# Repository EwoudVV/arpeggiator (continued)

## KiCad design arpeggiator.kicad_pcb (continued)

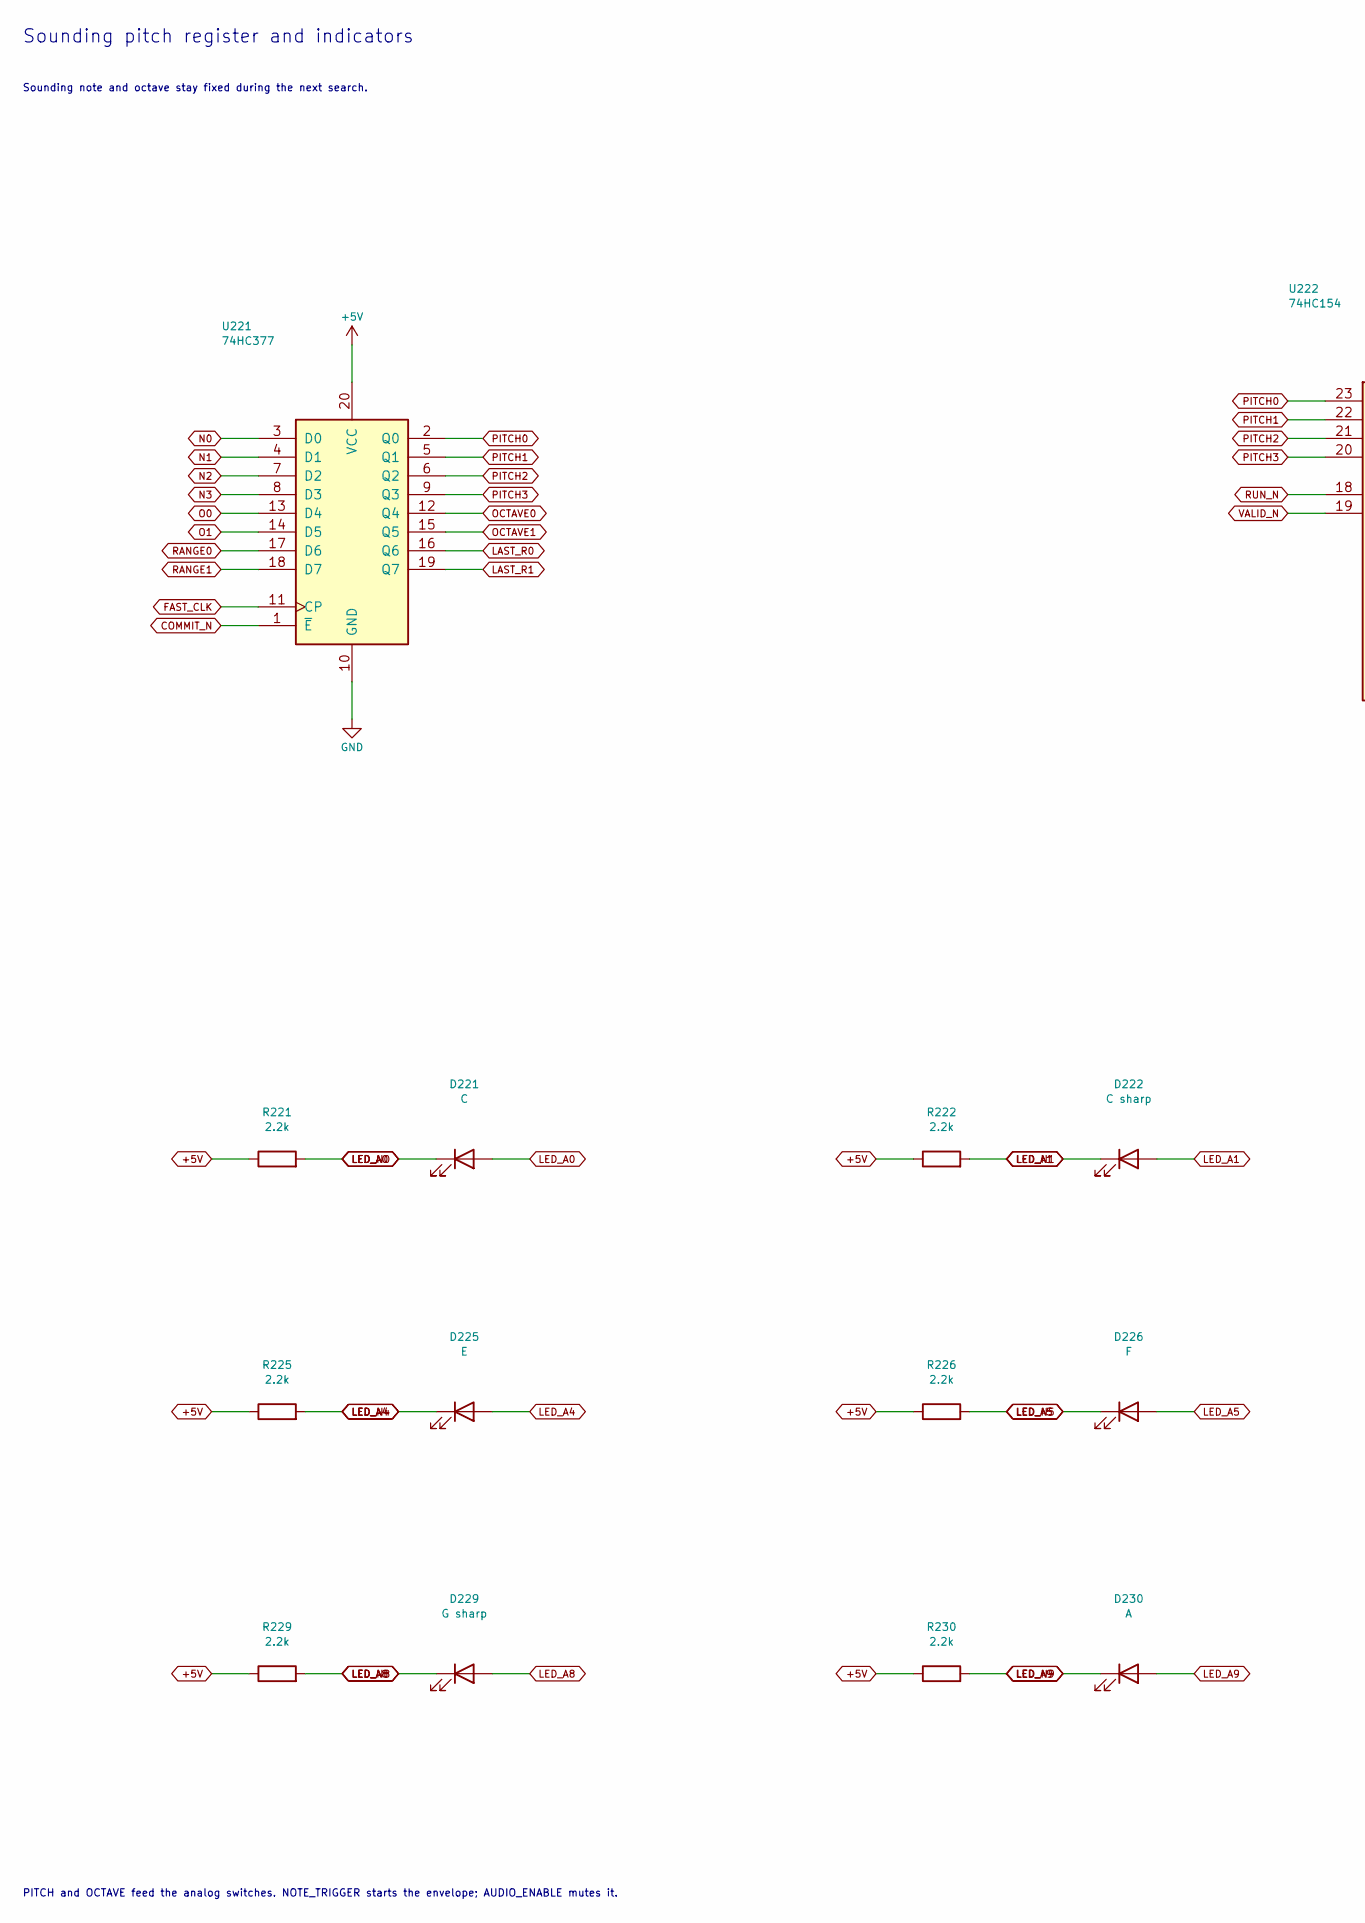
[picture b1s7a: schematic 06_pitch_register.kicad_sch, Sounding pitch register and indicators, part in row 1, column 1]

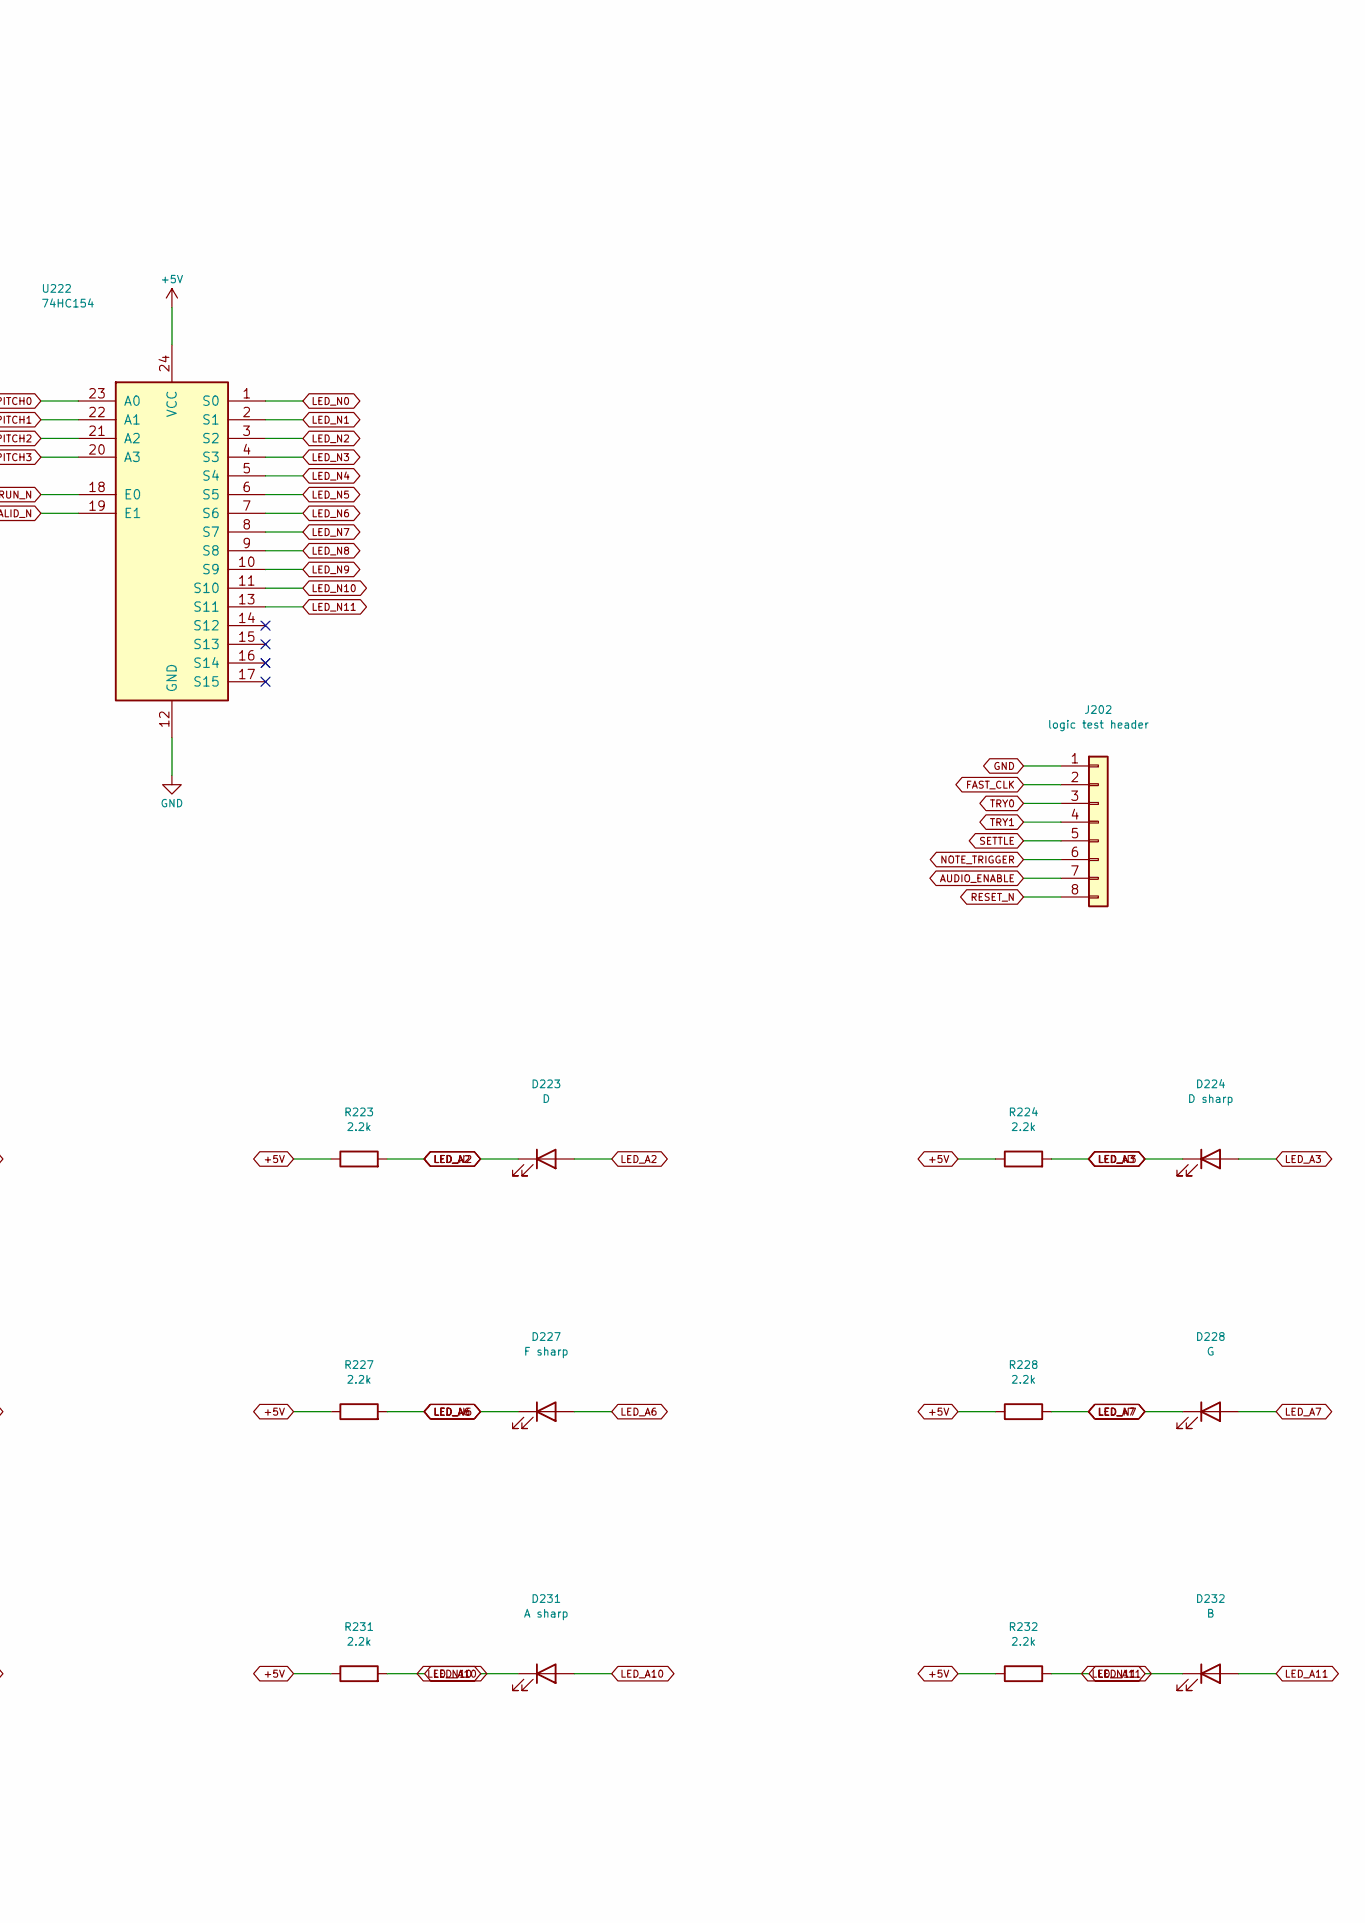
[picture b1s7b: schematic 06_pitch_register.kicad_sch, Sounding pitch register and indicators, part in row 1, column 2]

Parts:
D221: C; LED_0805_2012Metric
D222: C sharp; LED_0805_2012Metric
D223: D; LED_0805_2012Metric
D224: D sharp; LED_0805_2012Metric
D225: E; LED_0805_2012Metric
D226: F; LED_0805_2012Metric
D227: F sharp; LED_0805_2012Metric
D228: G; LED_0805_2012Metric
D229: G sharp; LED_0805_2012Metric
D230: A; LED_0805_2012Metric
D231: A sharp; LED_0805_2012Metric
D232: B; LED_0805_2012Metric
J202: logic test header; PinHeader_1x08_P2.54mm_Vertical
R221, R222, R223, R224, R225, R226, R227, R228, R229, R230, R231, R232: 2.2k; R_0805_2012Metric
U221: 74HC377; SOIC-20W_7.5x12.8mm_P1.27mm; MPN 74HC377D,653
U222: 74HC154; SOIC-24W_7.5x15.4mm_P1.27mm; MPN CD74HC154M96

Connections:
+5V: R221.1, R222.1, R223.1, R224.1, R225.1, R226.1, R227.1, R228.1, R229.1, R230.1, R231.1, R232.1, U221.20 (VCC), U222.24 (VCC); also elsewhere on the board
AUDIO_ENABLE: J202.7; also elsewhere on the board
COMMIT_N: U221.1 (~E); also elsewhere on the board
FAST_CLK: J202.2, U221.11 (CP); also elsewhere on the board
LAST_R0: U221.16 (Q6); also elsewhere on the board
LAST_R1: U221.19 (Q7); also elsewhere on the board
LED_A0: D221.2 (A), R221.2
LED_A1: D222.2 (A), R222.2
LED_A2: D223.2 (A), R223.2
LED_A3: D224.2 (A), R224.2
LED_A4: D225.2 (A), R225.2
LED_A5: D226.2 (A), R226.2
LED_A6: D227.2 (A), R227.2
LED_A7: D228.2 (A), R228.2
LED_A8: D229.2 (A), R229.2
LED_A9: D230.2 (A), R230.2
LED_A10: D231.2 (A), R231.2
LED_A11: D232.2 (A), R232.2
LED_N0: D221.1 (K), U222.1 (S0)
LED_N1: D222.1 (K), U222.2 (S1)
LED_N2: D223.1 (K), U222.3 (S2)
LED_N3: D224.1 (K), U222.4 (S3)
LED_N4: D225.1 (K), U222.5 (S4)
LED_N5: D226.1 (K), U222.6 (S5)
LED_N6: D227.1 (K), U222.7 (S6)
LED_N7: D228.1 (K), U222.8 (S7)
LED_N8: D229.1 (K), U222.9 (S8)
LED_N9: D230.1 (K), U222.10 (S9)
LED_N10: D231.1 (K), U222.11 (S10)
LED_N11: D232.1 (K), U222.13 (S11)
N0: U221.3 (D0); also elsewhere on the board
N1: U221.4 (D1); also elsewhere on the board
N2: U221.7 (D2); also elsewhere on the board
N3: U221.8 (D3); also elsewhere on the board
NOTE_TRIGGER: J202.6; also elsewhere on the board
O0: U221.13 (D4); also elsewhere on the board
O1: U221.14 (D5); also elsewhere on the board
OCTAVE0: U221.12 (Q4); also elsewhere on the board
OCTAVE1: U221.15 (Q5); also elsewhere on the board
PITCH0: U221.2 (Q0), U222.23 (A0); also elsewhere on the board
PITCH1: U221.5 (Q1), U222.22 (A1); also elsewhere on the board
PITCH2: U221.6 (Q2), U222.21 (A2); also elsewhere on the board
PITCH3: U221.9 (Q3), U222.20 (A3); also elsewhere on the board
RANGE0: U221.17 (D6); also elsewhere on the board
RANGE1: U221.18 (D7); also elsewhere on the board
RESET_N: J202.8; also elsewhere on the board
RUN_N: U222.18 (E0); also elsewhere on the board
SETTLE: J202.5; also elsewhere on the board
TRY0: J202.3; also elsewhere on the board
TRY1: J202.4; also elsewhere on the board
VALID_N: U222.19 (E1); also elsewhere on the board

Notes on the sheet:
Sounding pitch register and indicators
Sounding note and octave stay fixed during the next search.
PITCH and OCTAVE feed the analog switches. NOTE_TRIGGER starts the envelope; AUDIO_ENABLE mutes it.

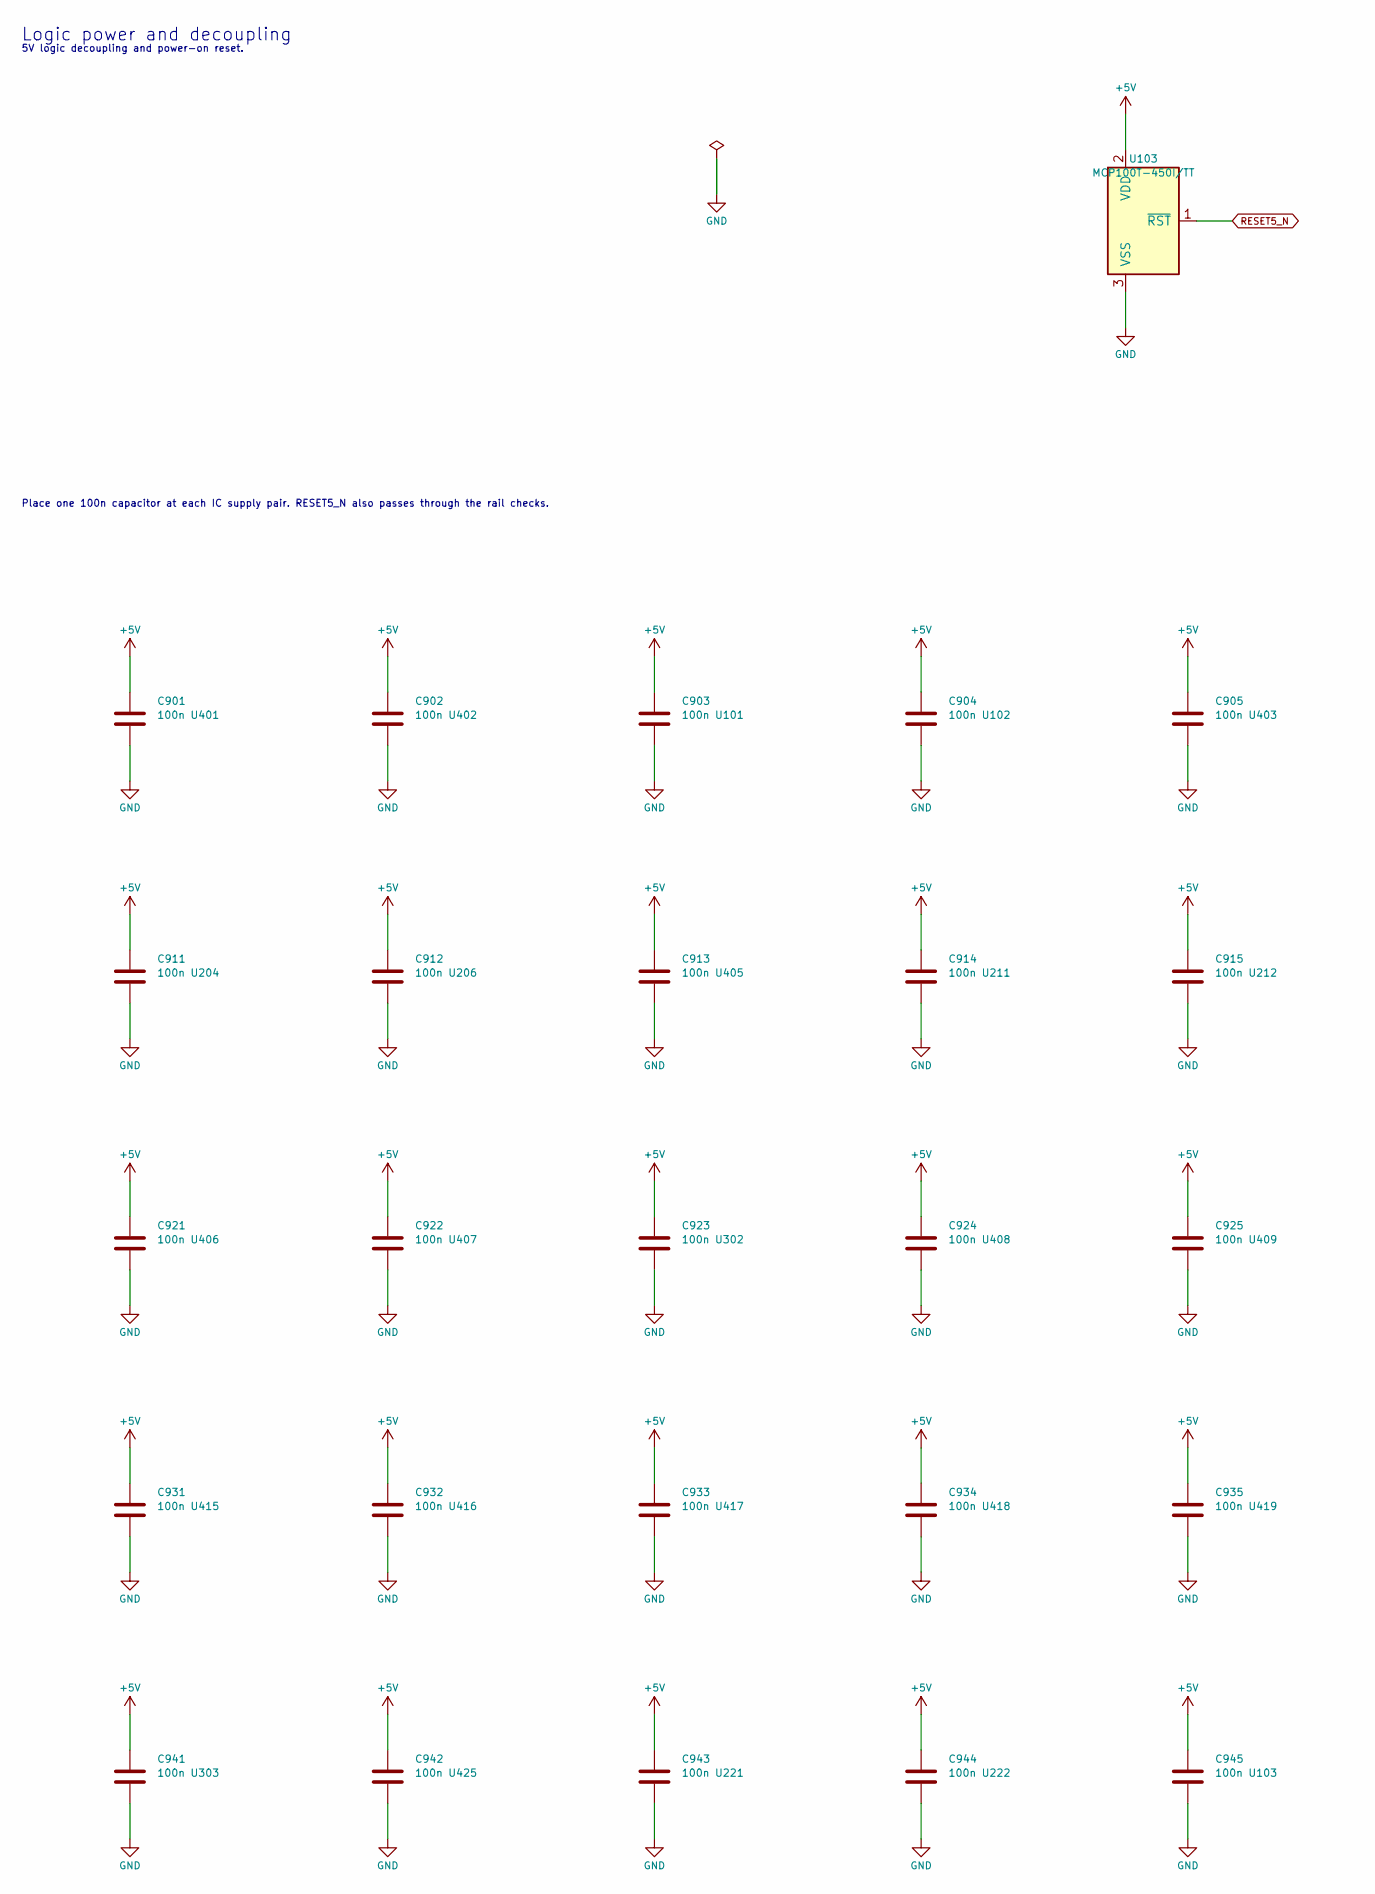
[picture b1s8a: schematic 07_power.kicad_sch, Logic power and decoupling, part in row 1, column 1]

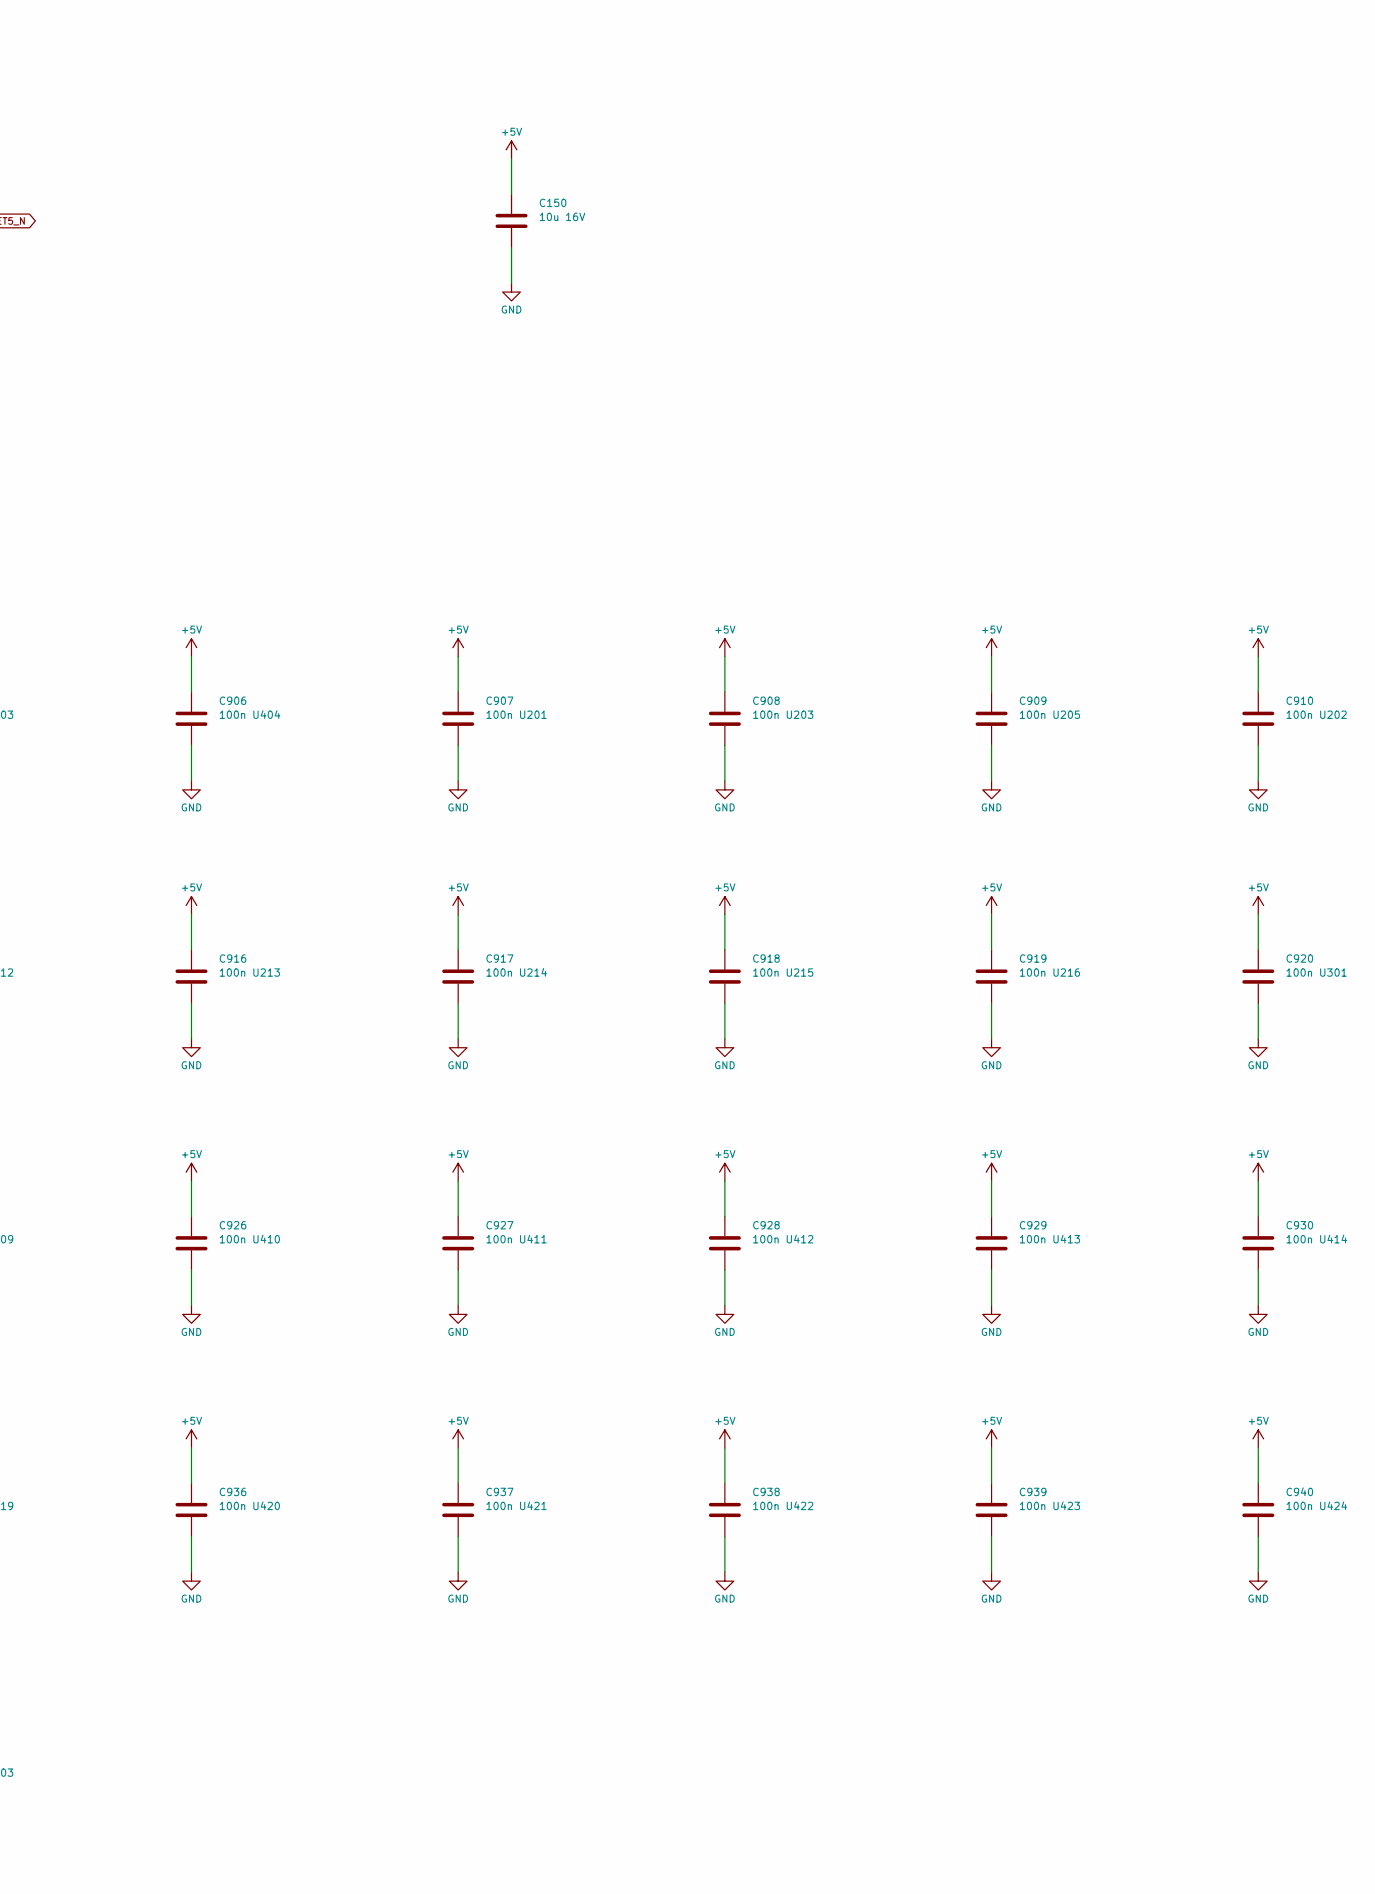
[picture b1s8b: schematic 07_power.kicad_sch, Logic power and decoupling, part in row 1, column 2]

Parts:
C150: 10u 16V; C_0805_2012Metric
C901: 100n U401; C_0805_2012Metric
C902: 100n U402; C_0805_2012Metric
C903: 100n U101; C_0805_2012Metric
C904: 100n U102; C_0805_2012Metric
C905: 100n U403; C_0805_2012Metric
C906: 100n U404; C_0805_2012Metric
C907: 100n U201; C_0805_2012Metric
C908: 100n U203; C_0805_2012Metric
C909: 100n U205; C_0805_2012Metric
C910: 100n U202; C_0805_2012Metric
C911: 100n U204; C_0805_2012Metric
C912: 100n U206; C_0805_2012Metric
C913: 100n U405; C_0805_2012Metric
C914: 100n U211; C_0805_2012Metric
C915: 100n U212; C_0805_2012Metric
C916: 100n U213; C_0805_2012Metric
C917: 100n U214; C_0805_2012Metric
C918: 100n U215; C_0805_2012Metric
C919: 100n U216; C_0805_2012Metric
C920: 100n U301; C_0805_2012Metric
C921: 100n U406; C_0805_2012Metric
C922: 100n U407; C_0805_2012Metric
C923: 100n U302; C_0805_2012Metric
C924: 100n U408; C_0805_2012Metric
C925: 100n U409; C_0805_2012Metric
C926: 100n U410; C_0805_2012Metric
C927: 100n U411; C_0805_2012Metric
C928: 100n U412; C_0805_2012Metric
C929: 100n U413; C_0805_2012Metric
C930: 100n U414; C_0805_2012Metric
C931: 100n U415; C_0805_2012Metric
C932: 100n U416; C_0805_2012Metric
C933: 100n U417; C_0805_2012Metric
C934: 100n U418; C_0805_2012Metric
C935: 100n U419; C_0805_2012Metric
C936: 100n U420; C_0805_2012Metric
C937: 100n U421; C_0805_2012Metric
C938: 100n U422; C_0805_2012Metric
C939: 100n U423; C_0805_2012Metric
C940: 100n U424; C_0805_2012Metric
C941: 100n U303; C_0805_2012Metric
C942: 100n U425; C_0805_2012Metric
C943: 100n U221; C_0805_2012Metric
C944: 100n U222; C_0805_2012Metric
C945: 100n U103; C_0805_2012Metric
U103: MCP100T-450I/TT; SOT-23; MPN MCP100T-450I/TT

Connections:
+5V: C150.1, C901.1, C902.1, C903.1, C904.1, C905.1, C906.1, C907.1, C908.1, C909.1, C910.1, C911.1, C912.1, C913.1, C914.1, C915.1, C916.1, C917.1, C918.1, C919.1, C920.1, C921.1, C922.1, C923.1, C924.1, C925.1, C926.1, C927.1, C928.1, C929.1, C930.1, C931.1, C932.1, C933.1, C934.1, C935.1, C936.1, C937.1, C938.1, C939.1, C940.1, C941.1, C942.1, C943.1, C944.1, C945.1, U103.2 (VDD); also elsewhere on the board
RESET5_N: U103.1 (~RST); also elsewhere on the board

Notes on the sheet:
Logic power and decoupling
5V logic decoupling and power-on reset.
Place one 100n capacitor at each IC supply pair. RESET5_N also passes through the rail checks.

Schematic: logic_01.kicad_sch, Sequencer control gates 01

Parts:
U401, U402, U403: 74HC14; SOIC-14_3.9x8.7mm_P1.27mm; MPN 74HC14D,653
U404: 74HC04; SOIC-14_3.9x8.7mm_P1.27mm; MPN 74HC04D,653

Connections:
+5V: U401.14 (VCC), U402.14 (VCC), U403.14 (VCC), U404.14 (VCC); also elsewhere on the board
ADVANCE: U404.12; also elsewhere on the board
ADVANCE_N: U404.13; also elsewhere on the board
CAPTURE: U404.8; also elsewhere on the board
CAPTURE_N: U404.9; also elsewhere on the board
IDLE: U404.6; also elsewhere on the board
IDLE_N: U404.5; also elsewhere on the board
RANGE_IN0: U404.2; also elsewhere on the board
RANGE_IN1: U404.4; also elsewhere on the board
RANGE_INV0: U403.8, U404.1
RANGE_INV1: U403.10, U404.3
RANGE_RC0: U403.9; also elsewhere on the board
RANGE_RC1: U403.11; also elsewhere on the board
SEED: U404.10; also elsewhere on the board
SEED_N: U404.11; also elsewhere on the board

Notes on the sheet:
Sequencer control gates 01

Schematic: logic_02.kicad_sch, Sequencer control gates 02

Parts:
U405, U408, U416: 74HC04; SOIC-14_3.9x8.7mm_P1.27mm; MPN 74HC04D,653
U420: 74HC14; SOIC-14_3.9x8.7mm_P1.27mm; MPN 74HC14D,653

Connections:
+5V: U405.14 (VCC), U408.14 (VCC), U416.14 (VCC), U420.14 (VCC); also elsewhere on the board
ABORT: U420.5; also elsewhere on the board
ANY_NOTE: U420.3; also elsewhere on the board
BUTTON_LAST: U405.11; also elsewhere on the board
CAPTURE: U416.9; also elsewhere on the board
CHECK: U405.2; also elsewhere on the board
CHECK_N: U405.1; also elsewhere on the board
COMMIT: U405.4; also elsewhere on the board
COMMIT_N: U405.3; also elsewhere on the board
G028: U405.10; also elsewhere on the board
G030: U405.12; also elsewhere on the board
G033: U408.2; also elsewhere on the board
G037: U408.4; also elsewhere on the board
G054: U408.6; also elsewhere on the board
G058: U408.10; also elsewhere on the board
G063: U408.13; also elsewhere on the board
G064: U408.12; also elsewhere on the board
G065: U416.1; also elsewhere on the board
G066: U416.2; also elsewhere on the board
G068: U416.4; also elsewhere on the board
G070: U416.5; also elsewhere on the board
G071: U416.6; also elsewhere on the board
G073: U416.8; also elsewhere on the board
G076: U416.10; also elsewhere on the board
G078: U416.12; also elsewhere on the board
G084: U420.2; also elsewhere on the board
G090: U420.4; also elsewhere on the board
G096: U420.6; also elsewhere on the board
G100: U420.9; also elsewhere on the board
IDLE: U408.3; also elsewhere on the board
N2: U408.11; also elsewhere on the board
NOTE_HIT: U420.1; also elsewhere on the board
OCT_EN: U416.3; also elsewhere on the board
RANGE0: U416.13; also elsewhere on the board
RANGE1: U416.11; also elsewhere on the board
RESEED: U408.9; also elsewhere on the board
RUN_LAST: U408.1; also elsewhere on the board
SEED_LOAD_N: U408.8; also elsewhere on the board
SETTLE: U405.6; also elsewhere on the board
SETTLE_N: U405.5; also elsewhere on the board
STATE_LOAD_N: U420.8; also elsewhere on the board
TEMPO_LAST: U405.13; also elsewhere on the board
TRIGGER: U405.8; also elsewhere on the board
TRIGGER_N: U405.9; also elsewhere on the board
VALID: U408.5; also elsewhere on the board

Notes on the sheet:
Sequencer control gates 02

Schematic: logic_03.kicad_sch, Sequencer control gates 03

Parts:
U406, U413, U414, U417: 74HC08; SOIC-14_3.9x8.7mm_P1.27mm; MPN 74HC08D,653

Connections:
+5V: U406.14 (VCC), U413.14 (VCC), U414.14 (VCC), U417.14 (VCC); also elsewhere on the board
ADVANCE: U414.4; also elsewhere on the board
BAD_RANGE: U413.3; also elsewhere on the board
BUTTON_EDGE: U406.3; also elsewhere on the board
BUTTON_SYNC: U406.1; also elsewhere on the board
G028: U406.2; also elsewhere on the board
G030: U406.5; also elsewhere on the board
G033: U406.10; also elsewhere on the board
G035: U406.13; also elsewhere on the board
G055: U413.5; also elsewhere on the board
G058: U413.10; also elsewhere on the board
G059: U413.8, U414.1
G060: U413.11, U414.2
G064: U414.9; also elsewhere on the board
G066: U414.10; also elsewhere on the board
G068: U414.13; also elsewhere on the board
G070: U417.3; also elsewhere on the board
G071: U417.5; also elsewhere on the board
G073: U417.10; also elsewhere on the board
G075: U417.11; also elsewhere on the board
LAST_NOTE: U414.3, U414.5
LAST_OCT: U414.8, U417.2
N0: U413.13; also elsewhere on the board
N1: U413.12; also elsewhere on the board
N2: U417.13; also elsewhere on the board
N3: U413.9, U417.12; also elsewhere on the board
NOTE_RESET_N: U414.11; also elsewhere on the board
OCT_EN: U414.6, U417.1; also elsewhere on the board
OCT_RESET_N: U417.6; also elsewhere on the board
RANGE0: U413.1; also elsewhere on the board
RANGE1: U413.2; also elsewhere on the board
RESEED: U413.6; also elsewhere on the board
RESET_N: U414.12, U417.4, U417.9; also elsewhere on the board
RUN: U406.9, U406.12; also elsewhere on the board
RUN_EDGE: U406.8; also elsewhere on the board
SEED: U413.4; also elsewhere on the board
STEP_REQ: U406.11; also elsewhere on the board
TEMPO_EDGE: U406.6; also elsewhere on the board
TEMPO_SYNC: U406.4; also elsewhere on the board
TRY_RESET_N: U417.8; also elsewhere on the board

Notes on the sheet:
Sequencer control gates 03

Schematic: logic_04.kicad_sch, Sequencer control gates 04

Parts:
U418, U421, U423, U425: 74HC08; SOIC-14_3.9x8.7mm_P1.27mm; MPN 74HC08D,653

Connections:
+5V: U418.14 (VCC), U421.14 (VCC), U423.14 (VCC), U425.14 (VCC); also elsewhere on the board
AUDIO_ENABLE: U425.3; also elsewhere on the board
CHECK: U421.4, U421.12; also elsewhere on the board
EMPTY_ABORT: U421.8; also elsewhere on the board
G066: U418.4; also elsewhere on the board
G076: U418.2; also elsewhere on the board
G077: U418.3; also elsewhere on the board
G078: U418.10; also elsewhere on the board
G079: U418.6, U418.9
G080: U418.8; also elsewhere on the board
G084: U421.2, U421.13; also elsewhere on the board
G085: U418.11, U421.1
G086: U421.3; also elsewhere on the board
G088: U421.5; also elsewhere on the board
G091: U421.10; also elsewhere on the board
G096: U423.2, U423.10; also elsewhere on the board
G097: U421.11, U423.1
G102: U423.4; also elsewhere on the board
G103: U423.6, U423.9
G105: U423.11, U425.1
O0: U418.5; also elsewhere on the board
O1: U418.1; also elsewhere on the board
RESET_N: U425.2, U425.9; also elsewhere on the board
RETRY: U423.3; also elsewhere on the board
RUN: U423.5, U423.12, U425.10; also elsewhere on the board
SEARCH_FAULT: U421.6; also elsewhere on the board
SEED: U421.9; also elsewhere on the board
TRIGGER: U425.4; also elsewhere on the board
TRIGGER_D: U425.6; also elsewhere on the board
TRIGGER_RESET_N: U425.8; also elsewhere on the board
TRY2: U418.13; also elsewhere on the board
TRY3: U418.12; also elsewhere on the board
VALID: U423.13, U425.5; also elsewhere on the board
VALID_D: U423.8; also elsewhere on the board

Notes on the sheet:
Sequencer control gates 04

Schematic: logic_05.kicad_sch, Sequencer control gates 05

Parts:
U407, U415: 74HC86; SOIC-14_3.9x8.7mm_P1.27mm; MPN 74HC86D,653
U409, U410: 74HC32; SOIC-14_3.9x8.7mm_P1.27mm; MPN 74HC32D,653

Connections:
+5V: U407.14 (VCC), U409.14 (VCC), U410.14 (VCC), U415.14 (VCC); also elsewhere on the board
BUTTON_EDGE: U407.2; also elsewhere on the board
G035: U409.3; also elsewhere on the board
G037: U409.4; also elsewhere on the board
G039: U409.8; also elsewhere on the board
G040: U409.11; also elsewhere on the board
G041: U410.3; also elsewhere on the board
G042: U410.6; also elsewhere on the board
G043: U410.8; also elsewhere on the board
G044: U410.11; also elsewhere on the board
G051: U407.6; also elsewhere on the board
G052: U407.8; also elsewhere on the board
G063: U407.11; also elsewhere on the board
G065: U415.3; also elsewhere on the board
LAST_R0: U407.5; also elsewhere on the board
LAST_R1: U407.10; also elsewhere on the board
NOTE_SNAP0: U409.9; also elsewhere on the board
NOTE_SNAP1: U409.10; also elsewhere on the board
NOTE_SNAP2: U409.12; also elsewhere on the board
NOTE_SNAP3: U409.13; also elsewhere on the board
NOTE_SNAP4: U410.1; also elsewhere on the board
NOTE_SNAP5: U410.2; also elsewhere on the board
NOTE_SNAP6: U410.4; also elsewhere on the board
NOTE_SNAP7: U410.5; also elsewhere on the board
NOTE_SNAP8: U410.9; also elsewhere on the board
NOTE_SNAP9: U410.10; also elsewhere on the board
NOTE_SNAP10: U410.12; also elsewhere on the board
NOTE_SNAP11: U410.13; also elsewhere on the board
O0: U407.12; also elsewhere on the board
O1: U415.1; also elsewhere on the board
RANGE0: U407.4, U407.13; also elsewhere on the board
RANGE1: U407.9, U415.2; also elsewhere on the board
RUN: U407.1; also elsewhere on the board
RUN_D: U407.3; also elsewhere on the board
RUN_EDGE: U409.2; also elsewhere on the board
STATE_EN: U409.6; also elsewhere on the board
STEP_REQ: U409.5; also elsewhere on the board
TEMPO_EDGE: U409.1; also elsewhere on the board

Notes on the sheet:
Sequencer control gates 05

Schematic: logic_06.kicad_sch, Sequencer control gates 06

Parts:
U411, U412, U419, U422: 74HC32; SOIC-14_3.9x8.7mm_P1.27mm; MPN 74HC32D,653

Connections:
+5V: U411.14 (VCC), U412.14 (VCC), U419.14 (VCC), U422.14 (VCC); also elsewhere on the board
ABORT: U422.11; also elsewhere on the board
ANY_NOTE: U412.3; also elsewhere on the board
BAD_RANGE: U422.1; also elsewhere on the board
EMPTY_ABORT: U422.9; also elsewhere on the board
G039: U411.1; also elsewhere on the board
G040: U411.2; also elsewhere on the board
G041: U411.4; also elsewhere on the board
G042: U411.5; also elsewhere on the board
G043: U411.9; also elsewhere on the board
G044: U411.10; also elsewhere on the board
G045: U411.3, U411.12
G046: U411.6, U411.13
G047: U411.8, U412.2
G048: U411.11, U412.1
G051: U412.4; also elsewhere on the board
G052: U412.5; also elsewhere on the board
G054: U412.9; also elsewhere on the board
G055: U412.8; also elsewhere on the board
G075: U419.9; also elsewhere on the board
G077: U419.1; also elsewhere on the board
G080: U419.2; also elsewhere on the board
G081: U412.11, U419.4
G082: U419.3, U419.5
G083: U419.6, U419.10
G086: U419.13; also elsewhere on the board
G087: U419.8, U419.12
G088: U419.11; also elsewhere on the board
G090: U422.2; also elsewhere on the board
G091: U422.3; also elsewhere on the board
G093: U422.6, U422.12
G094: U422.8, U422.13
O2: U412.13; also elsewhere on the board
O3: U412.12; also elsewhere on the board
RANGE_CHANGED: U412.6, U412.10
RUN_N: U422.4; also elsewhere on the board
SEARCH_FAULT: U422.10; also elsewhere on the board
ST3: U422.5; also elsewhere on the board

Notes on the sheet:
Sequencer control gates 06

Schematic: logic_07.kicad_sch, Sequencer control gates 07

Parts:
U424: 74HC32; SOIC-14_3.9x8.7mm_P1.27mm; MPN 74HC32D,653

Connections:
+5V: U424.14 (VCC); also elsewhere on the board
ABORT: U424.5; also elsewhere on the board
COMMIT: U424.10; also elsewhere on the board
G099: U424.3, U424.4
G100: U424.6; also elsewhere on the board
G102: U424.8; also elsewhere on the board
RETRY: U424.1; also elsewhere on the board
TRIGGER: U424.2; also elsewhere on the board
VALID: U424.9; also elsewhere on the board

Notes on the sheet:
Sequencer control gates 07

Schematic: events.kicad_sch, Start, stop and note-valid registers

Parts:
U301, U302, U303: 74HC74; SOIC-14_3.9x8.7mm_P1.27mm; MPN 74HC74D,653

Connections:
+5V: U301.4 (~S), U301.10 (~S), U301.14 (VCC), U302.4 (~S), U302.10 (~S), U302.14 (VCC), U303.4 (~S), U303.10 (~S), U303.14 (VCC); also elsewhere on the board
BUTTON_LAST: U301.5 (Q); also elsewhere on the board
BUTTON_SYNC: U301.2 (D); also elsewhere on the board
FAST_CLK: U301.3 (C), U301.11 (C), U302.3 (C), U302.11 (C), U303.3 (C), U303.11 (C); also elsewhere on the board
NOTE_TRIGGER: U303.9 (Q); also elsewhere on the board
RESET_N: U301.1 (~R), U301.13 (~R), U302.1 (~R), U302.13 (~R), U303.1 (~R); also elsewhere on the board
RUN: U302.5 (Q), U302.12 (D); also elsewhere on the board
RUN_D: U302.2 (D); also elsewhere on the board
RUN_LAST: U302.9 (Q); also elsewhere on the board
RUN_N: U302.6 (~Q); also elsewhere on the board
TEMPO_LAST: U301.9 (Q); also elsewhere on the board
TEMPO_SYNC: U301.12 (D); also elsewhere on the board
TRIGGER_D: U303.12 (D); also elsewhere on the board
TRIGGER_RESET_N: U303.13 (~R); also elsewhere on the board
VALID: U303.5 (Q); also elsewhere on the board
VALID_D: U303.2 (D); also elsewhere on the board
VALID_N: U303.6 (~Q); also elsewhere on the board

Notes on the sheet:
Start, stop and note-valid registers
Event inputs are synchronized before edge detection. Reset forces RUN and VALID low.

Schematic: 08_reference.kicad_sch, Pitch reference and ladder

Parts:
C501: 100n; C_0805_2012Metric
D501: LM4040A25IDBZR; SOT-23; MPN LM4040A25IDBZR
R501: 2.49k; R_0805_2012Metric
R502: 15k 0.1% 25ppm/C; R_0805_2012Metric
R503: 10k 0.1% 25ppm/C; R_0805_2012Metric
R504, R505: 10k 0.01% 25ppm/C; R_0805_2012Metric; MPN RNCF0805TKY10K0
R511, R512, R513, R514, R515, R516, R517, R518, R519, R520, R521, R522: 1k 0.1%; R_0805_2012Metric
U501: OPA4192IDR; SOIC-14_3.9x8.7mm_P1.27mm; MPN OPA4192IDR

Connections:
+5V: R501.1; also elsewhere on the board
unnamed: R502.2, R503.1, U501.3 (+)
unnamed: R504.1, R505.2, U501.6 (-)
REF1V: R522.1, U501.1 (OUT), U501.2 (-), U501.5 (+); also elsewhere on the board
REF2V: R505.1, U501.7 (OUT); also elsewhere on the board
REF2V5: C501.1, D501.1 (K), R501.2, R502.1; also elsewhere on the board
TAP1: R511.1, R512.2; also elsewhere on the board
TAP2: R512.1, R513.2; also elsewhere on the board
TAP3: R513.1, R514.2; also elsewhere on the board
TAP4: R514.1, R515.2; also elsewhere on the board
TAP5: R515.1, R516.2; also elsewhere on the board
TAP6: R516.1, R517.2; also elsewhere on the board
TAP7: R517.1, R518.2; also elsewhere on the board
TAP8: R518.1, R519.2; also elsewhere on the board
TAP9: R519.1, R520.2; also elsewhere on the board
TAP10: R520.1, R521.2; also elsewhere on the board
TAP11: R521.1, R522.2; also elsewhere on the board

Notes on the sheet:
Pitch reference and ladder
2.5V reference. U501A makes 1V, U501B makes 2V. Precision ratios set the pitch span.
Twelve equal sections. C is ground; C sharp through B use TAP1 through TAP11.
